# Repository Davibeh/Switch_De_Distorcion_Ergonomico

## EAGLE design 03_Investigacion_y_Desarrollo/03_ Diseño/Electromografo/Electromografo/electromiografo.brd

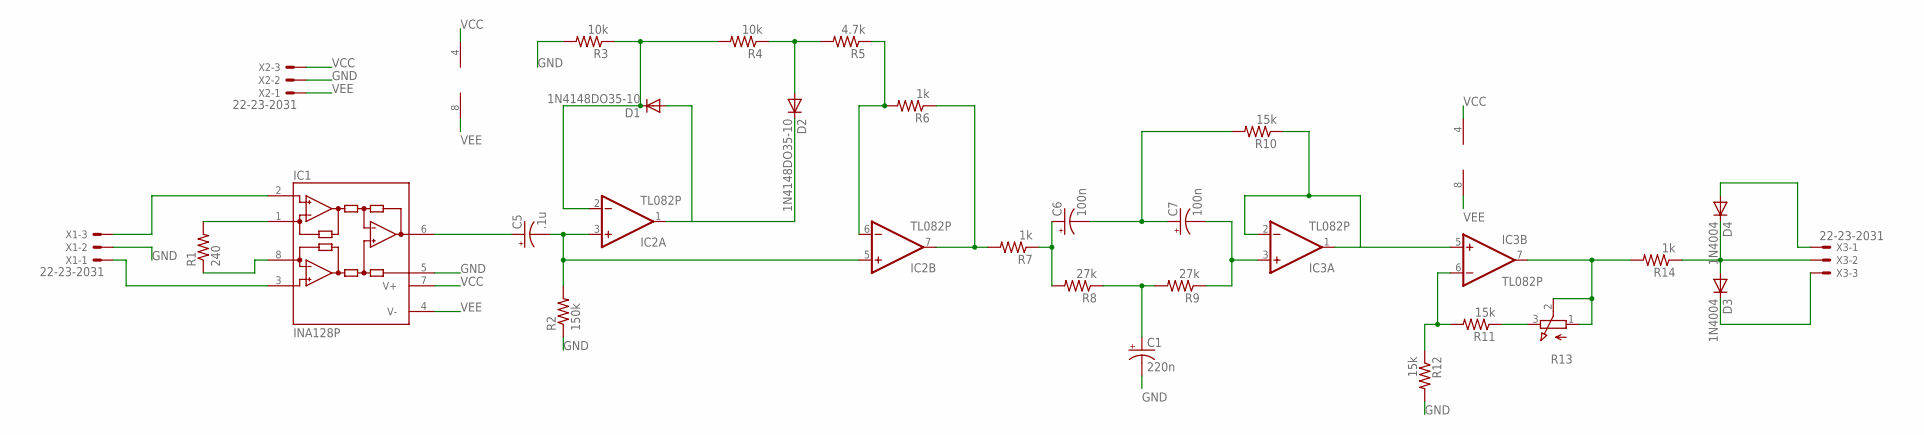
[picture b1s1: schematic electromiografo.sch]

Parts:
C1: 220n; E2-5
C5: .1u; E2-5
C6, C7: 100n; E2-5
D1, D2: 1N4148DO35-10; DO35-10
D3, D4: 1N4004; DO41-10
IC1: INA128P; DIL08
IC2, IC3: TL082P; DIL08
R1: 240; 0207/12
R2: 150k; 0207/12
R3, R4: 10k; 0207/12
R5: 4.7k; 0207/12
R6, R7, R14: 1k; 0207/12
R8, R9: 27k; 0207/12
R10, R11, R12: 15k; 0207/12
R13: 3RP/1610N
X1, X2, X3: 22-23-2031

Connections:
GND: C1.-, IC1.5 (REF), R2.1, R3.2, R12.2, X1.2, X2.2
unnamed: IC1.2 (-IN), X1.3
unnamed: IC1.1 (RG), R1.2
unnamed: IC1.8 (RG), R1.1
unnamed: IC1.3 (+IN), X1.1
unnamed: D1.C, IC2.2 (-IN), R3.1, R4.2
unnamed: C6.+, R7.1, R8.2
unnamed: C5.-, IC2.3 (+IN), IC2.5 (+IN), R2.2
unnamed: C6.-, C7.+, R10.2
unnamed: C5.+, IC1.6 (OUT)
unnamed: C1.+, R8.1, R9.2
unnamed: C7.-, IC3.3 (+IN), R9.1
unnamed: IC3.1 (OUT), IC3.2 (-IN), IC3.5 (+IN), R10.1
unnamed: D1.A, D2.C, IC2.1 (OUT)
unnamed: D2.A, R4.1, R5.2
unnamed: IC2.6 (-IN), R5.1, R6.2
unnamed: IC2.7 (OUT), R6.1, R7.2
unnamed: IC3.6 (-IN), R11.2, R12.1
unnamed: R11.1, R13.3 (E)
unnamed: IC3.7 (OUT), R13.1 (A), R13.2 (S), R14.2
unnamed: D3.A, D4.C, R14.1, X3.2
unnamed: D4.A, X3.1
unnamed: D3.C, X3.3
VCC: IC1.7 (V+), IC2.4 (V-), IC3.4 (V-), X2.3
VEE: IC1.4 (V-), IC2.8 (V+), IC3.8 (V+), X2.1

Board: 2 copper layers, 28 parts (0 on the bottom side), 25 nets, no tracks yet.

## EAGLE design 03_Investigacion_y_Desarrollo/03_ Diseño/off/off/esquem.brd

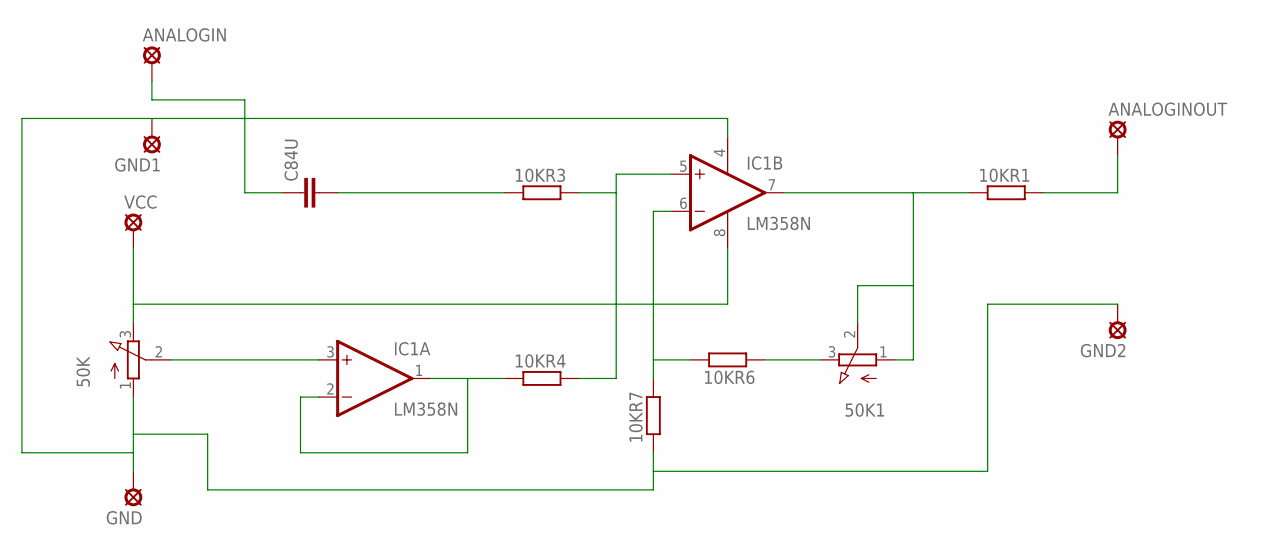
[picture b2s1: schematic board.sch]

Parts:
10KR1, 10KR3, 10KR4, 10KR6, 10KR7: R-EU_0411/12; 0411/12
50K, 50K1: 3RP/1610N
ANALOGIN: SE11
ANALOGINOUT: SE11
C84U: C2.5/6; C2.5-6
GND, GND1, GND2: SE11
IC1: LM358N; DIL08
VCC: SE11

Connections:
100KR1: 10KR1.1, 50K1.1 (A), 50K1.2 (S), IC1.7 (OUT)
GND: 10KR7.1, 50K.1 (A), GND.MP, GND1.MP, GND2.MP, IC1.4 (V-)
unnamed: 50K.2 (S), IC1.3 (+IN)
unnamed: 10KR4.1, IC1.1 (OUT), IC1.2 (-IN)
unnamed: 10KR3.2, 10KR4.2, IC1.5 (+IN)
unnamed: 10KR3.1, C84U.2
unnamed: ANALOGIN.MP, C84U.1
unnamed: 10KR6.2, 10KR7.2, IC1.6 (-IN)
unnamed: 10KR6.1, 50K1.3 (E)
unnamed: 10KR1.2, ANALOGINOUT.MP
VCC: 50K.3 (E), IC1.8 (V+), VCC.MP

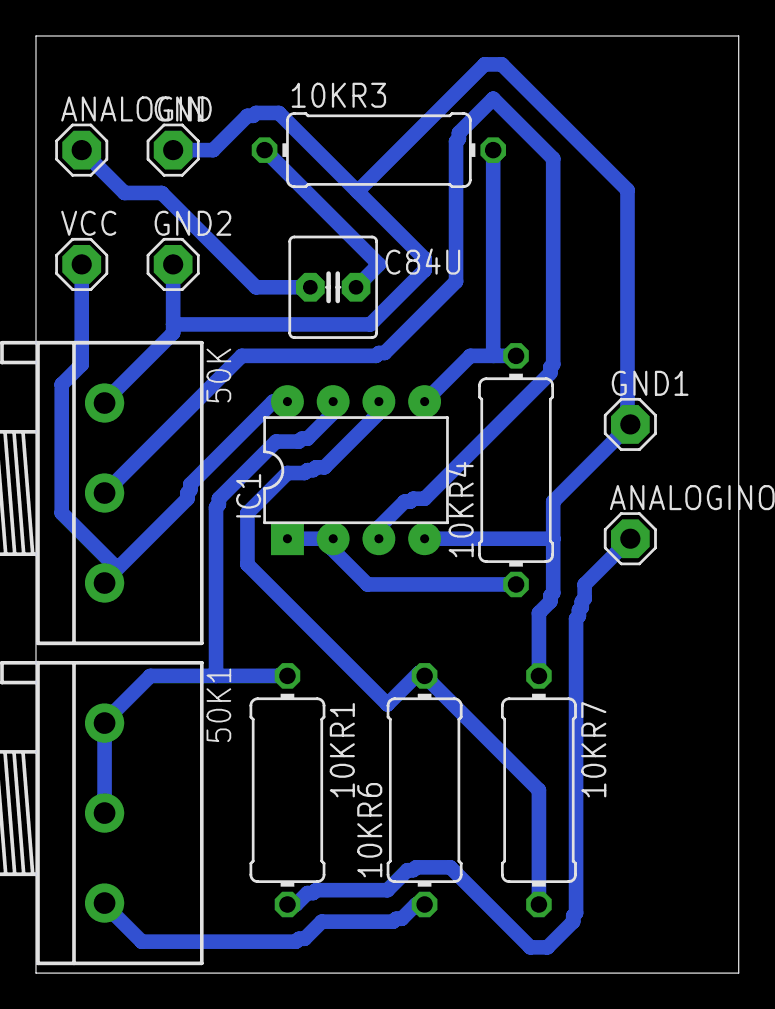
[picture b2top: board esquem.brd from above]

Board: 2 copper layers, 39.0 x 52.1 mm, 15 parts (0 on the bottom side), 11 nets.

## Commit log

2018-03-30 Primera configuración
    Primera configuración del proyecto:
    1- Se agregaron los folder y un archivo que describe el contenido de los mismos
    2- Se agregaron los archios de finanzas, los planes de proyecto, la architectura de HW y SW.
    3- Se agregón un documento manual para abir la arquitectura de SW y HW-
    4- Se creo un proyecto en MCU xpresso
2018-03-31 First integration of Alfa and Beta Software
    Consiste en la inclusion de las funcionalidades de efectos de sonido en la conifiguracíon de sistema provista por MCU expresso
2018-04-01 Segund Integración del SW alfa
    Se integráron las funciones de efecto de sonido Vibrato y Distorción.
    Al parecer vibrato no funciona se levantó el issue #9
2018-04-01 Third Integraton of Alpah Beta variants
    This is the first full integration of the alfpha beta variants.
    The Scheduler is not working properly, the loop never reaches the task execution, the workaround is to use the 1ms PIT IRQ and execute the 1ms taks there.
    Need to analyze if the problem can be solved an use the correct Scheduler.
    The movement is dected but with the Computer the voltage suplly makes the EMG to vary to much in a way that is not detectable by the SW. the normal averge voltage is 1300 counts that corresponds to 1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
    This issue is known and it needs the board disconnected form the computer, unfurtunatelly is not possible right now there is and iss
2018-04-01 Cambios de configuración proyecto MCUxpresso y WBS
    Se agregó el WBS de Chung.
    Se cambió la configuración en mcuxpresso de manaera que ahora es factible el utulizar la configuración "release" y "debug".
2018-04-12 Add files via upload
    se agregaron puntos visto en clase
    Nota. versiones anteriores de ambos documentos se encuentran los comentarios de los respectivos issues
2018-04-12 cambio en fases
    se agrego la fase de planeacion en project charter y en la presentación
2018-04-12 Formato proyect charter
    Cambio en el formato el proyect charter
2018-04-24 Commit de Entrega
    Subir todos los archivos y cambios relizados ene l proyecto.
2018-04-24 REmover archivo duplicado
